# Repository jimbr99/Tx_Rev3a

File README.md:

# Tx_Rev3a
Wireless Power Transfer transmitter rev 3a PCB documents
Wireless Power Transfer transmitter rev 3a PCB documents
Contains hardware build information for the Onda Corp. Wireless Power Transfer transmitter board revision 3a.

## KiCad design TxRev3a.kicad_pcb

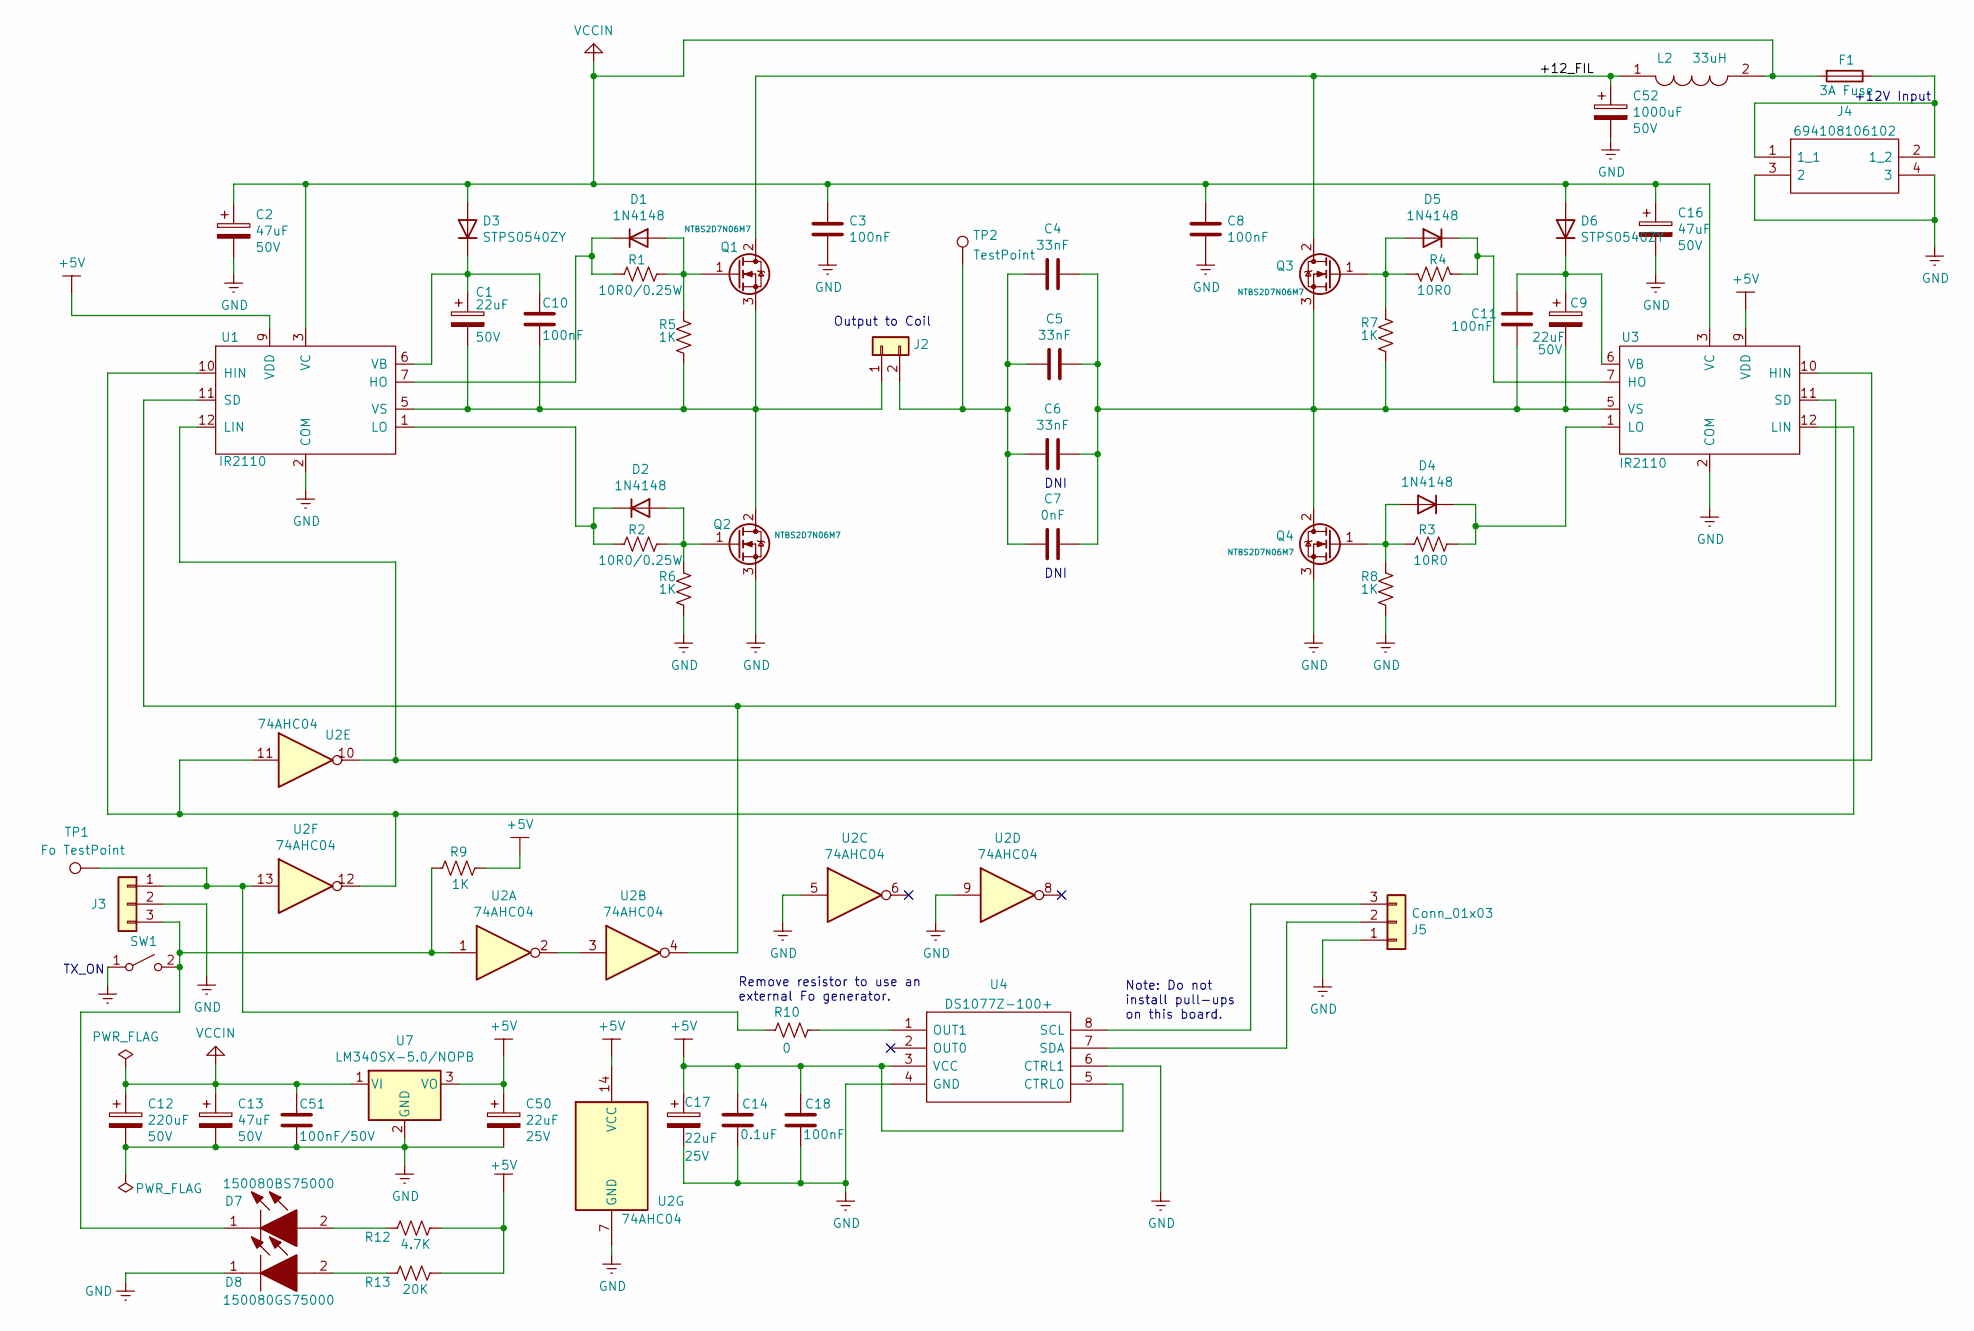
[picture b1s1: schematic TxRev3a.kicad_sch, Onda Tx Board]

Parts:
C1, C9: 22uF; CP_Radial_D5.0mm_P2.50mm; Voltage 50V
C2, C13, C16: 47uF; CP_Radial_D6.3mm_P2.50mm; Voltage 50V
C3, C8, C10, C11, C18: 100nF; C_0603_1608Metric_Pad1.08x0.95mm_HandSolder
C4, C5, C6: 33nF; C_1210_3225Metric
C7: 0nF; C_1210_3225Metric
C12: 220uF; CP_Radial_D10.0mm_P5.00mm; Voltage 50V
C14: 0.1uF; C_0402_1005Metric
C17, C50: 22uF; CP_Radial_D5.0mm_P2.50mm; Voltage 25V
C51: 100nF/50V; C_0603_1608Metric_Pad1.08x0.95mm_HandSolder
C52: 1000uF; CP_Radial_D13.0mm_P5.00mm; Voltage 50V
D1, D2, D4, D5: 1N4148; D_DO-35_SOD27_P7.62mm_Horizontal
D3, D6: STPS0540ZY; D_DO-41_SOD81_P10.16mm_Horizontal
D7: 150080BS75000; LEDM2012X80N; Mouser Part Number 710-150080GS75000
D8: 150080GS75000; LEDM2012X80N; Mouser Part Number 710-150080GS75000
F1: 3A Fuse; Fuse_1206_3216Metric
J2: Conn_01x02; PhoenixContact_MCV_1,5_2-G-5.08_1x02_P5.08mm_Vertical
J3, J5: Conn_01x03; Molex_KK-254_AE-6410-03A_1x03_P2.54mm_Vertical
J4: 694108106102; Mouser Part Number 710-694108106102
L2: 33uH; INDPM120120X805N; Mouser Part Number 994-MSS1278-333MLD
Q1, Q2, Q3, Q4: NTBS2D7N06M7; TO-263-2
R1, R2: 10R0/0.25W; R_0805_2012Metric
R3, R4: 10R0; R_0805_2012Metric
R5, R6, R7, R8, R9: 1K; R_0805_2012Metric
R10: 0; R_0805_2012Metric
R12: 4.7K; R_0805_2012Metric
R13: 20K; R_0805_2012Metric
SW1: SW_SPST; Molex_KK-254_AE-6410-02A_1x02_P2.54mm_Vertical
TP1: Fo TestPoint; PinSocket_1x01_P2.54mm_Vertical
TP2: TestPoint
U1, U3: IR2110; DIP-14_W7.62mm
U2: 74AHC04; DIP-14_W7.62mm
U4: DS1077Z-100+; SOIC127P600X175-8N; Mouser Part Number 700-DS1077Z-100
U7: LM340SX-5.0/NOPB; TO-220-3_Vertical

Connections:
+5V: C14.1, C17.1, C18.1, C50.1, R9.1, R12.1, R13.1, U1.9 (VDD), U2.14 (VCC), U3.9 (VDD), U4.3 (VCC), U4.5 (CTRL0), U7.3 (VO)
/+12_FIL: C52.1, L2.1, Q1.2 (D), Q3.2 (D)
GND: C2.2, C3.2, C8.2, C12.2, C13.2, C14.2, C16.2, C17.2, C18.2, C50.2, C51.2, C52.2, D8.1, J3.2, J4.3 (2), J4.4 (3), J5.1, Q2.3 (S), Q4.3 (S), R6.2, R8.2, SW1.1 (A), U1.2 (COM), U2.5, U2.7 (GND), U2.9, U3.2 (COM), U4.4 (GND), U4.6 (CTRL1), U7.2 (GND)
unnamed: C1.1, C10.1, D3.1 (K), U1.6 (VB)
unnamed: C1.2, C10.2, J2.1, Q1.3 (S), Q2.2 (D), R5.2, U1.5 (VS)
unnamed: C4.1, C5.1, C6.1, C7.1, J2.2, TP2.1
unnamed: C9.1, C11.1, D6.1 (K), U3.6 (VB)
unnamed: C4.2, C5.2, C6.2, C7.2, C9.2, C11.2, Q3.3 (S), Q4.2 (D), R7.2, U3.5 (VS)
unnamed: D1.1 (K), R1.1, U1.7 (HO)
unnamed: D1.2 (A), Q1.1 (G), R1.2, R5.1
unnamed: D2.1 (K), R2.1, U1.1 (LO)
unnamed: D2.2 (A), Q2.1 (G), R2.2, R6.1
unnamed: D4.1 (K), R3.2, U3.1 (LO)
unnamed: D4.2 (A), Q4.1 (G), R3.1, R8.1
unnamed: D5.1 (K), R4.1, U3.7 (HO)
unnamed: D5.2 (A), Q3.1 (G), R4.2, R7.1
unnamed: D7.1, J3.3, R9.2, SW1.2 (B), U2.1
unnamed: D7.2, R12.2
unnamed: D8.2, R13.2
unnamed: F1.1, J4.1 (1_1), J4.2 (1_2)
unnamed: J3.1, R10.1, TP1.1, U2.13
unnamed: J5.2, U4.7 (SDA)
unnamed: J5.3, U4.8 (SCL)
unnamed: R10.2, U4.1 (OUT1)
unnamed: U1.10 (HIN), U2.11, U2.12, U3.12 (LIN)
unnamed: U1.11 (SD), U2.4, U3.11 (SD)
unnamed: U1.12 (LIN), U2.10, U3.10 (HIN)
unnamed: U2.2, U2.3
VCCIN: C2.1, C3.1, C8.1, C12.1, C13.1, C16.1, C51.1, D3.2 (A), D6.2 (A), F1.2, L2.2, U1.3 (VC), U3.3 (VC), U7.1 (VI); also elsewhere on the board

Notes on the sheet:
DNI
Output to Coil
TX_ON
Remove resistor to use an external Fo generator.
Note: Do not install pull-ups on this board.
+12V Input

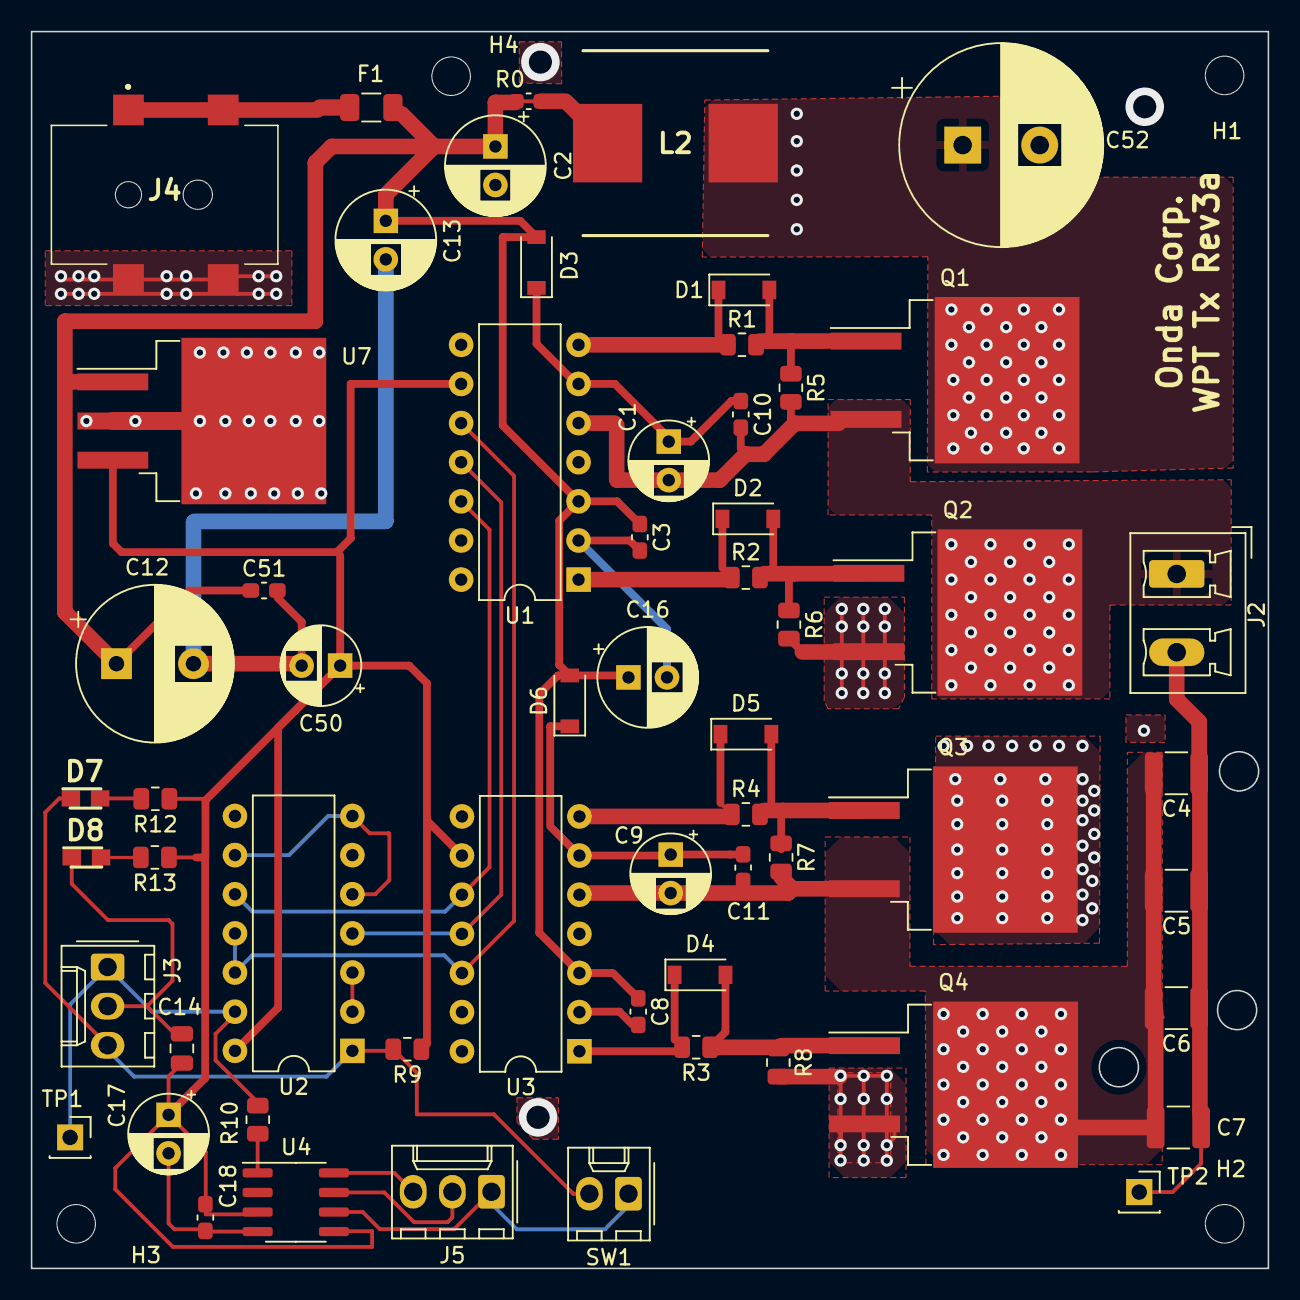
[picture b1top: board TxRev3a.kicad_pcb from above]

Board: 4 copper layers, 80.3 x 80.3 mm, 63 parts (0 on the bottom side), 29 nets.

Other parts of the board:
H1, H2, H3, H4: MountingHole_2.5mm
R0: C_0603_1608Metric

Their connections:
VCCIN: R0.1, R0.2; also elsewhere on the board

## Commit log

2022-11-07 :lollipop: Added .gitattributes & .gitignore files
2022-11-07 Initial TxRev3a repo
